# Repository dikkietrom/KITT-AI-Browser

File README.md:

to prevent

<pre>
Error: The module <your dir>\KITT\node_modules\robotjs\build\Release\robotjs.node'
was compiled against a different Node.js version using
NODE_MODULE_VERSION 108. This version of Node.js requires
NODE_MODULE_VERSION 113. Please try re-compiling or re-installing
the module (for instance, using npm rebuild or npm install).
</pre>
first do once
<pre>
rm -rf node_modules
rm package-lock.json
npm install
./node_modules/.bin/electron-rebuild
</pre>
then every time you want to start
<pre>
npm start
</pre>
to make binary apps for win mac & lin do
<pre>
npm run build
</pre>

whereafter generated binaries can be found in ./dist

# KITT AI Browser
"KITT In Twenty Three"

Introducing the new KITT on the block for all your AI browsing, developments and execution. 
An advanced path based AI plugin system that focuses on easily chaining
AI IO to improve efficiency, accuracy, and overall performance. A powerful AI-driven frontend app built on 
the Electron framework, 
designed to give you seamless control over local and online AI based services and 
websites without the obligation for API keys. 
KITT utilizes Electron's WebView feature, enabling full remote control of any 
hosted service. For additional flexibility, API key integration 
is available when required.

KITT currently includes the following plugins 
<pre>
- agent-gpt
- bark
- bash
- broker
- ceo-test
- coder
- dall-e
- elevenlabs
- feed
- file
- google
- gpt
- gpt-api-hack
- gpt-edit
- midjourney
- open-assistant
- summariser
- user
- whisper
- youtube
</pre>

Harness the power of open-source Chromium and experience the unparalleled control offered by KITT for all your web-based projects. With KITT, the possibilities are endless.

Video's

https://www.youtube.com/@dik9091/videos

KITT features a user-friendly plugin architecture that makes extending its capabilities a breeze. By simply adding files to the dedicated plugin directory, you can effortlessly integrate new functionalities and enhancements.

This modular approach allows developers to create, share, and implement custom plugins tailored to specific needs. Each plugin file is automatically detected and loaded by KITT, eliminating the need for manual configuration or setup.

The plugin system fosters a collaborative environment, encouraging the community to contribute to KITT's ever-expanding capabilities. With this straightforward architecture, KITT becomes a versatile and adaptable tool, ready to tackle any challenge you throw its way.

The project structure :
<pre>
├── README.md
├── back-end
│   ├── ipcMain.js
│   ├── keys.js
│   └── main.js
├── front-end
│   ├── class.css
│   ├── front-log.js
│   ├── id.css
│   ├── index.html
│   ├── index.js
│   ├── ipcRenderer.js
│   ├── main-log.js
│   ├── plugin-preload.js
│   ├── plugin.js
│   ├── preload-log.js
│   ├── preload.js
│   ├── tag.css
│   └── webgl.js
├── lib
│   └── shared.js
├── package-lock.json
├── package.json
├── plugins
│   ├── agent-gpt
│   │   ├── index.js
│   │   ├── main.js
│   │   └── preload.js
│   ├── bark
│   │   ├── index.js
│   │   └── main.js
│   ├── bash
│   │   ├── index.js
│   │   └── main.js
│   ├── broker
│   │   └── index.js
│   ├── ceo-test
│   │   ├── index.html
│   │   ├── index.js
│   │   ├── main.js
│   │   └── preload.js
│   ├── coder
│   │   ├── code.js
│   │   ├── index.html
│   │   ├── index.js
│   │   └── main.js
│   ├── dall-e
│   │   ├── index.js
│   │   └── main.js
│   ├── elevenlabs
│   │   ├── index.js
│   │   ├── main.js
│   │   └── speak.py
│   ├── feed
│   │   ├── index.js
│   │   └── main.js
│   ├── file
│   │   ├── index.js
│   │   └── main.js
│   ├── google
│   │   ├── index.js
│   │   ├── main.js
│   │   └── preload.js
│   ├── gpt
│   │   ├── index.js
│   │   └── main.js
│   ├── gpt-api-hack
│   │   ├── index.js
│   │   └── main.js
│   ├── gpt-edit
│   │   ├── index.js
│   │   └── main.js
│   ├── midjourney
│   │   ├── index.js
│   │   ├── main.js
│   │   └── preload.js
│   ├── open-assistant
│   │   ├── index.js
│   │   ├── main.js
│   │   └── preload.js
│   ├── summariser
│   │   ├── index.js
│   │   └── main.js
│   ├── user
│   │   └── index.js
│   ├── whisper
│   │   ├── index.js
│   │   └── main.js
│   └── youtube
│       ├── index.js
│       ├── main.js
│       └── preload.js
└── wintel-builder-config.json
</pre>

The main components of the system include:

Back-end: Contains the main process of the Electron app, with files like ipcMain.js and main.js to handle inter-process communication and the main application window management.

Front-end: This part consists of the renderer process of the Electron app, with files like index.html, index.js, and various CSS files for styling. It also contains the IPC renderer files and the webGL for audio visualization.

Plugins: The system features multiple plugins, each providing specific functionality. Some of the plugins include agent-gpt, bark, bash, broker, coder, dall-e, elevenlabs, feed, file, google, gpt, gpt-api-hack, gpt-edit, midjourney, open-assistant, summariser, user, whisper, and youtube.

Shared Library: The lib folder contains shared.js, which presumably contains shared code or utility functions that can be used across the system.

Configuration and Package Files: The system has package.json, package-lock.json, and wintel-builder-config.json files for managing dependencies, build configurations, and application settings.

In summary, this system is a desktop application built on Electron, designed to accommodate various plugins and functionalities, primarily focused on AI models, multimedia processing, and web services.

---

**Overview Summary** 
<pre>
└── back-end
    ├── ipcMain.js
    ├── keys.js
    └── main.js
</pre>
This project is an Electron application that consists of multiple JavaScript files handling different aspects of the application. The application uses Electron's IPC communication for message passing between the main and renderer processes. The application also has a plugin system that allows for extensibility.

1. **ipcMain.js** - Handles IPC communication, plugin initialization, and other miscellaneous functions.
2. **keys.js** - Manages API keys, prompts user for input and handles key storage.
3. **main.js** - Initializes the main Electron window, handles auto-updating, and other app-related events.

---

**Detailed API Documentation**
<pre>
└── back-end
    ├── ipcMain.js
    ├── keys.js
    └── main.js
</pre>
1. **ipcMain.js**

   Functions:

    - `init(lg)`: Initializes the ipcMain module with a given logger function.
    - `initPlugins()`: Scans the plugins folder, initializes each plugin's main and preload script if they exist, and sends a message to the renderer process with information about the plugins.

   IPC Events:

    - `plugin-request`: Triggers the plugin initialization process.
    - `debug`: Opens the developer tools for the renderer process.
    - `debug-stop`: Closes the developer tools for the renderer process.
    - `debug-main`: Opens the Chrome DevTools for the main process.
    - `debug-main-stop`: Closes the Chrome DevTools for the main process.
    - `preload-log`: Logs messages from the preload script.
    - `doInPreload`: Executes a function in the preload script.
    - `doInMain`: Executes a function in the main process.

2. **keys.js**

   Functions:

    - `apiKeys(kind)`: Retrieves the API key for a specified service from the keys folder.
    - `promptIt(title, kind)`: Prompts the user to enter an API key and saves it to the keys folder.
    - `mkdirs(dirPath)`: Creates the necessary directories for a given path if they don't exist.

3. **main.js**

   Functions:

    - `createWindow()`: Creates the main browser window for the application and sets up required event listeners.
    - `initMainScript(script)`: Initializes the main script for the application with the given script path.

   Electron App Events:

    - `ready`: Triggers the `createWindow()` function.
    - `web-contents-created`: Sets up the `will-attach-webview` event listener.
    - `window-all-closed`: Quits the app when all windows are closed.
    - `before-quit`, `quit`, `will-quit`: Closes any open Chrome instances before quitting the app.
    - `activate`: Recreates the main window if it was closed and the app is reactivated.

## Overview Summary

<pre>

└── front-end
    ├── class.css
    ├── front-log.js
    ├── id.css
    ├── index.html
    ├── index.js
    ├── ipcRenderer.js
    ├── main-log.js
    ├── plugin-preload.js
    ├── plugin.js
    ├── preload-log.js
    ├── preload.js
    ├── tag.css
    └── webgl.js

</pre>

The front-end consists of several JavaScript files that handle different aspects of the application. It includes:

1. `front-log.js`: Handles logging and error reporting in the front-end.
2. `index.js`: Main entry point for the application's front-end. It initializes and sets up event listeners.
3. `ipcRenderer.js`: Handles inter-process communication between the front-end and the main process.
4. `main-log.js`: Handles logging and error reporting in the main process.
5. `plugin-preload.js`: Preloads plugins and manages plugin-related operations.
6. `plugin.js`: Implements the core plugin functionality and provides an API for plugin management.
7. `preload-log.js`: Handles logging and error reporting during the preload phase.
8. `preload.js`: Sets up the Electron environment and makes necessary modules available for the front-end.
9. `webgl.js`: Implements audio visualization using WebGL and manages audio input from the user's microphone.

## Detailed API Documentation
<pre>

└── front-end
    ├── class.css
    ├── front-log.js
    ├── id.css
    ├── index.html
    ├── index.js
    ├── ipcRenderer.js
    ├── main-log.js
    ├── plugin-preload.js
    ├── plugin.js
    ├── preload-log.js
    ├── preload.js
    ├── tag.css
    └── webgl.js

</pre>

### `front-log.js`

- `addLog(logData)`: Adds a log entry with the specified data.
- `err(error)`: Logs an error message with the provided error object.

### `index.js`

- `init()`: Initializes the application and sets up event listeners.

### `ipcRenderer.js`

- No specific API functions, but it makes use of Electron's `ipcRenderer` module for inter-process communication.

### `main-log.js`

- `addLog(logData)`: Adds a log entry with the specified data.
- `err(error)`: Logs an error message with the provided error object.

### `plugin-preload.js`

- `loadPlugins()`: Loads and initializes all available plugins.
- `registerPlugin(plugin)`: Registers a plugin with the system.

###  `plugin.js` 

`plugin.js` defines and implements the Plugin class, which represents the core functionality for plugins in the application. Each plugin derives from this class and must override the `config()` and `exec()` methods. The Plugin class also manages plugin instances and categorizes them by name, directory, ID, and role.

### `Plugin Class`

##### Properties `Plugin Class`

- `async`: A boolean indicating if the plugin is asynchronous.
- `streamer`: A boolean indicating if the plugin is a streamer.
- `dir`: The plugin's directory.

##### Constructor

The constructor initializes a new instance of the Plugin class, setting its `async` and `streamer` properties to `false`. It also registers the plugin in various global objects by its name, directory, ID, and role.

##### Methods

- `onReplied(message)`: Called when a reply is received. Can be overridden by subclasses to implement custom behavior.
- `config()`: Should be overridden by subclasses to provide a configuration object with information about the plugin (e.g., name, id, role).
- `exec(message)`: Should be overridden by subclasses to implement the main functionality of the plugin.
- `onData(json)`: Called when data is received. Can be overridden by subclasses to implement custom behavior.
- `onTimeOut()`: Called when the plugin times out. Cleans up any pending tasks or resources.
- `startTimer()`: Starts a timer that will trigger `onTimeOut()` after 2000 ms.
- `stopTimer()`: Stops the timer started by `startTimer()`.
- `send(key, message)`: Sends a message with the specified key to the plugin's associated webView.

#### Functions

- `run()`: Starts the plugin execution process.
- `pluginReply(message)`: Handles a plugin's reply to a message.
- `newPluginReplyRow(plugin, cls)`: Creates a new table row for a plugin reply.
- `newInp(container)`: Creates a new input element for user interaction.
- `extractPluginDirFromAsar(path)`: Extracts the plugin directory from the given path.

### `preload-log.js`

- `preloadLog(event, mes)`: Logs a message with the provided event and message data.

### `preload.js`

- No specific API functions, but it sets up the Electron environment and makes necessary modules available for the front-end.

### `webgl.js`

- `animate()`: Updates the audio visualization based on the current audio input.
- `toHex(c)`: Converts a decimal number to its hexadecimal equivalent.
- `lerp(a, b, t)`: Linearly interpolates between two values based on a parameter t.
- `gradientToHex(t)`: Converts a gradient value to a corresponding RGB color in hexadecimal format.

Please note that this API documentation is based on the provided code snippets and might not cover all possible functionalities.

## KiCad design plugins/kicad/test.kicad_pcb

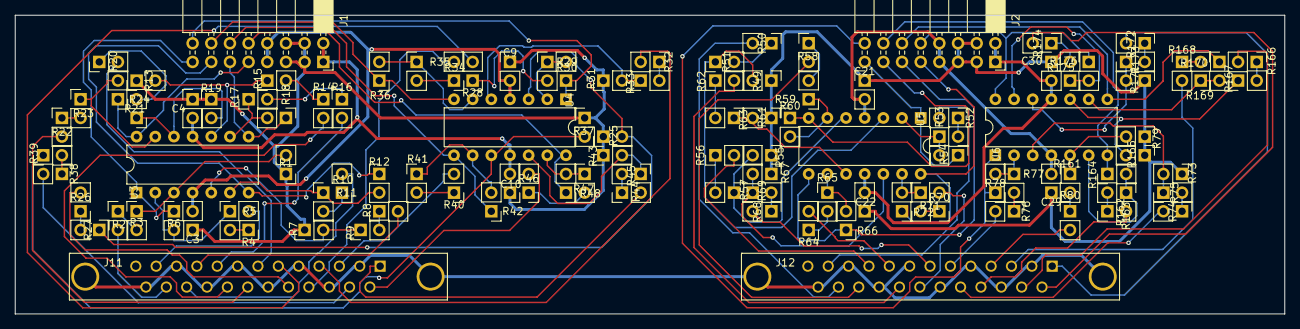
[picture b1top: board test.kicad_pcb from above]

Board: 2 copper layers, 172.7 x 40.6 mm, 112 parts (0 on the bottom side), 116 nets.

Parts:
C3, C4, C9, C10, C21, C22, C29, C30: 100n; PinHeader_1x02_P2.54mm_Vertical
J1, J2: CONN_02X08; PinSocket_2x08_P2.54mm_Horizontal
J11, J12: DB25_FEMALE; DB25FD
R1, R2, R3, R4, R5, R6, R7, R8, R9, R10, R11, R12, R13, R14, R15, R16, R17, R18, R19, R20, R21, R22, R23, R24, R25, R26, R27, R28, R29, R30, R31, R32, R33, R34, R35, R36, R37, R38, R39, R40, R41, R42, R43, R44, R45, R46, R47, R48, R49, R50, R51, R52, R53, R54, R55, R56, R57, R58, R59, R60, R61, R62, R63, R64, R65, R66, R67, R68, R69, R70, R71, R72, R73, R74, R75, R76, R77, R78, R79, R80, R161, R162, R163, R164, R165, R166, R167, R168, R169, R170, R171, R172, R173, R174, R175, R176: 10k; PinHeader_1x02_P2.54mm_Vertical
U3, U4, U5, U6: OPA4340D; DIP-14_W7.62mm

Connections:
+12V: C3.2, C9.2, C21.2, C29.2, J1.7, J1.8, J2.7, J2.8, U3.4, U4.4, U5.4, U6.4
-12V: C4.2, C10.2, C22.2, C30.2, J1.1, J1.2, J2.1, J2.2, U3.11, U4.11, U5.11, U6.11
/din1+: J11.24, R2.2
/din1-: J11.12, R4.2
/din2+: J11.10, R8.2
/din2-: J11.23, R10.2
/din3+: J11.21, R14.2
/din3-: J11.9, R16.2
/din4+: J11.7, R20.2
/din4-: J11.20, R22.2
/din5+: J11.18, R26.2
/din5-: J11.6, R28.2
/din6+: J11.4, R32.2
/din6-: J11.17, R34.2
/din7+: J11.15, R38.2
/din7-: J11.3, R40.2
/din8+: J11.1, R44.2
/din8-: J11.14, R46.2
/din9+: J12.24, R50.2
/din9-: J12.12, R52.2
/din10+: J12.10, R56.2
/din10-: J12.23, R58.2
/din11+: J12.21, R62.2
/din11-: J12.9, R64.2
/din12+: J12.7, R68.2
/din12-: J12.20, R70.2
/din13+: J12.18, R74.2
/din13-: J12.6, R76.2
/din14+: J12.4, R80.2
/din14-: J12.17, R162.2
/din15+: J12.15, R166.2
/din15-: J12.3, R168.2
/din16+: J12.1, R172.2
/din16-: J12.14, R174.2
/quad1/out1: J1.16, R30.1, U4.1
/quad1/out2: J1.14, R36.1, U4.7
/quad1/out3: J1.12, R42.1, U4.8
/quad1/out4: J1.10, R48.1, U4.14
/quad2/out1: J1.15, R6.1, U3.1
/quad2/out2: J1.13, R12.1, U3.7
/quad2/out3: J1.11, R18.1, U3.8
/quad2/out4: J1.9, R24.1, U3.14
/quad3/out1: J2.16, R78.1, U6.1
/quad3/out2: J2.14, R164.1, U6.7
/quad3/out3: J2.12, R170.1, U6.8
/quad3/out4: J2.10, R176.1, U6.14
/quad4/out1: J2.15, R54.1, U5.1
/quad4/out2: J2.13, R60.1, U5.7
/quad4/out3: J2.11, R66.1, U5.8
/quad4/out4: J2.9, R72.1, U5.14
GND: C3.1, C4.1, C9.1, C10.1, C21.1, C22.1, C29.1, C30.1, J1.3, J1.4, J1.5, J1.6, J2.3, J2.4, J2.5, J2.6, R1.1, R7.1, R13.1, R19.1, R25.1, R31.1, R37.1, R43.1, R49.1, R55.1, R61.1, R67.1, R73.1, R79.1, R165.1, R171.1
GNDPWR: J11.2, J11.5, J11.8, J11.11, J11.16, J11.19, J11.22, J11.25, J12.2, J12.5, J12.8, J12.11, J12.16, J12.19, J12.22, J12.25
unnamed: R1.2, R3.1, U3.3
unnamed: R2.1, R3.2
unnamed: R4.1, R5.2
unnamed: R5.1, R6.2, U3.2
unnamed: R7.2, R9.1, U3.5
unnamed: R8.1, R9.2
unnamed: R10.1, R11.2
unnamed: R11.1, R12.2, U3.6
unnamed: R13.2, R15.1, U3.10
unnamed: R14.1, R15.2
unnamed: R16.1, R17.2
unnamed: R17.1, R18.2, U3.9
unnamed: R19.2, R21.1, U3.12
unnamed: R20.1, R21.2
unnamed: R22.1, R23.2
unnamed: R23.1, R24.2, U3.13
unnamed: R25.2, R27.1, U4.3
unnamed: R26.1, R27.2
unnamed: R28.1, R29.2
unnamed: R29.1, R30.2, U4.2
unnamed: R31.2, R33.1, U4.5
unnamed: R32.1, R33.2
unnamed: R34.1, R35.2
unnamed: R35.1, R36.2, U4.6
unnamed: R37.2, R39.1, U4.10
unnamed: R38.1, R39.2
unnamed: R40.1, R41.2
unnamed: R41.1, R42.2, U4.9
unnamed: R43.2, R45.1, U4.12
unnamed: R44.1, R45.2
unnamed: R46.1, R47.2
unnamed: R47.1, R48.2, U4.13
unnamed: R49.2, R51.1, U5.3
unnamed: R50.1, R51.2
unnamed: R52.1, R53.2
unnamed: R53.1, R54.2, U5.2
unnamed: R55.2, R57.1, U5.5
unnamed: R56.1, R57.2
unnamed: R58.1, R59.2
unnamed: R59.1, R60.2, U5.6
unnamed: R61.2, R63.1, U5.10
unnamed: R62.1, R63.2
unnamed: R64.1, R65.2
unnamed: R65.1, R66.2, U5.9
unnamed: R67.2, R69.1, U5.12
unnamed: R68.1, R69.2
unnamed: R70.1, R71.2
unnamed: R71.1, R72.2, U5.13
unnamed: R73.2, R75.1, U6.3
unnamed: R74.1, R75.2
unnamed: R76.1, R77.2
unnamed: R77.1, R78.2, U6.2
unnamed: R79.2, R161.1, U6.5
unnamed: R80.1, R161.2
unnamed: R162.1, R163.2
unnamed: R163.1, R164.2, U6.6
unnamed: R165.2, R167.1, U6.10
unnamed: R166.1, R167.2
unnamed: R168.1, R169.2
unnamed: R169.1, R170.2, U6.9
unnamed: R171.2, R173.1, U6.12
unnamed: R172.1, R173.2
unnamed: R174.1, R175.2
unnamed: R175.1, R176.2, U6.13

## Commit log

2023-04-11 initial
2023-04-12 search added and refactor
2023-04-12 ignore keys
2023-04-12 stablish
2023-04-12 plugin arch stabl-ish
2023-04-12 all converted to plugin
2023-04-12 all converted to plugin stabl-ish
2023-04-13 added bash loopback
2023-04-14 central logging under control
2023-04-15 fix broken stuff
2023-04-18 broker in progress
2023-04-19 stable test
2023-04-20 testing chains
2023-04-21 chains tested ok with test plugins
2023-04-21 it is aIive
2023-04-21 reverse reply direction, release worthy now and ready for prod testing
2023-04-23 open assistant plugin stable, refactored gpt hack
2023-04-23 chains tested
2023-04-28 added data chunck feeder
2023-04-28 tested chunck feeder ok
2023-04-28 css vars , more styling
2023-04-28 broken webview preload fix
2023-04-29 testing coder
2023-04-29 auto code rollback pointer
2023-04-29 / escape for feeder content, tts and stt and bash as plugins
2023-05-01 coder tested, more styling
2023-05-01 coder fixes
2023-05-02 file plugin stable, first auto generated docs in README.md
2023-05-02 README.md format fix?
2023-05-02 README.md
2023-05-03 release fix issues
2023-05-03 bash testing
2023-05-04 bash plugin stable
2023-05-04 removed node-py and useGl = false
2023-05-06 testing nat-dev plugin
2023-05-06 Refactor session handling, remove decompression files, and update NatDev plugin
2023-05-06 bearer exposed fix auch
2023-05-06 remove "Sec-Fetch-Mode" header from nat-dev request
2023-05-07 Created using Colaboratory
2023-05-07 kicad + nanoGPT mockup
2023-05-27 perfectGPT
2023-05-29 no code
2023-05-30 pgpt
2023-05-31 pgpt crud
